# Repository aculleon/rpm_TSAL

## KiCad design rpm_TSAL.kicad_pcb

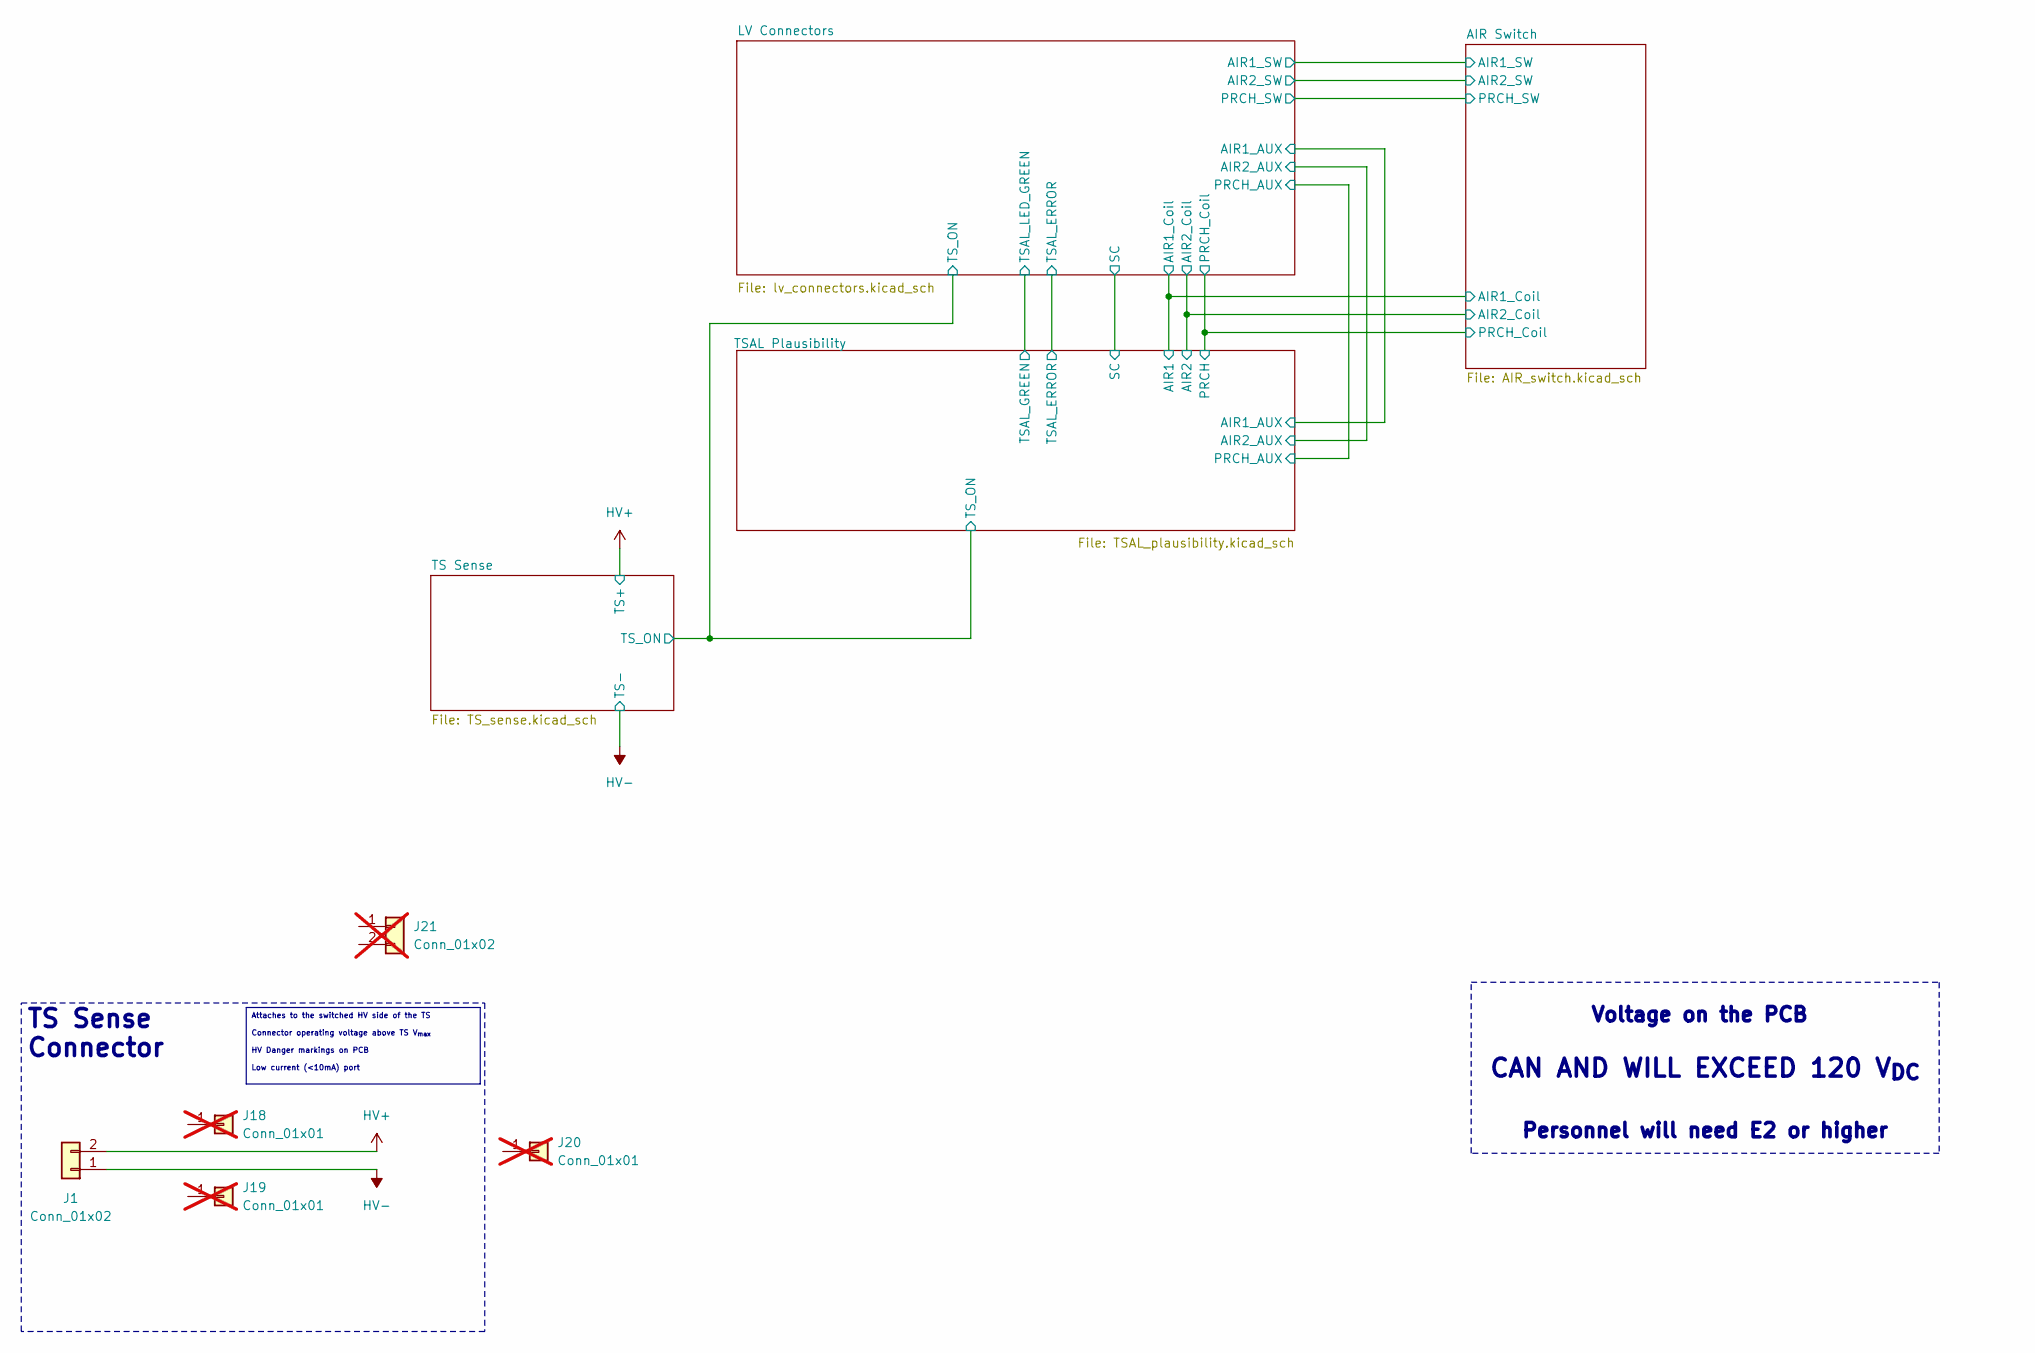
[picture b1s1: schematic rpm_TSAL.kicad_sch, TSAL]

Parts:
J1: Conn_01x02; 657002130101; Mouser 710-657002130101
J18, J19, J20: Conn_01x01; Mouser 710-65730513722DEC; not fitted
J21: Conn_01x02; Mouser 710-657002150201; not fitted

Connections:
HV+: J1.2; also elsewhere on the board
HV-: J1.1; also elsewhere on the board

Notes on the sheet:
_{Voltage on the PCB } CAN AND WILL EXCEED 120 V_{DC} _{Personnel will need E2 or higher}
Attaches to the switched HV side of the TS Connector operating voltage above TS V_{max} HV Danger markings on PCB Low current (<10mA) port
TS Sense Connector

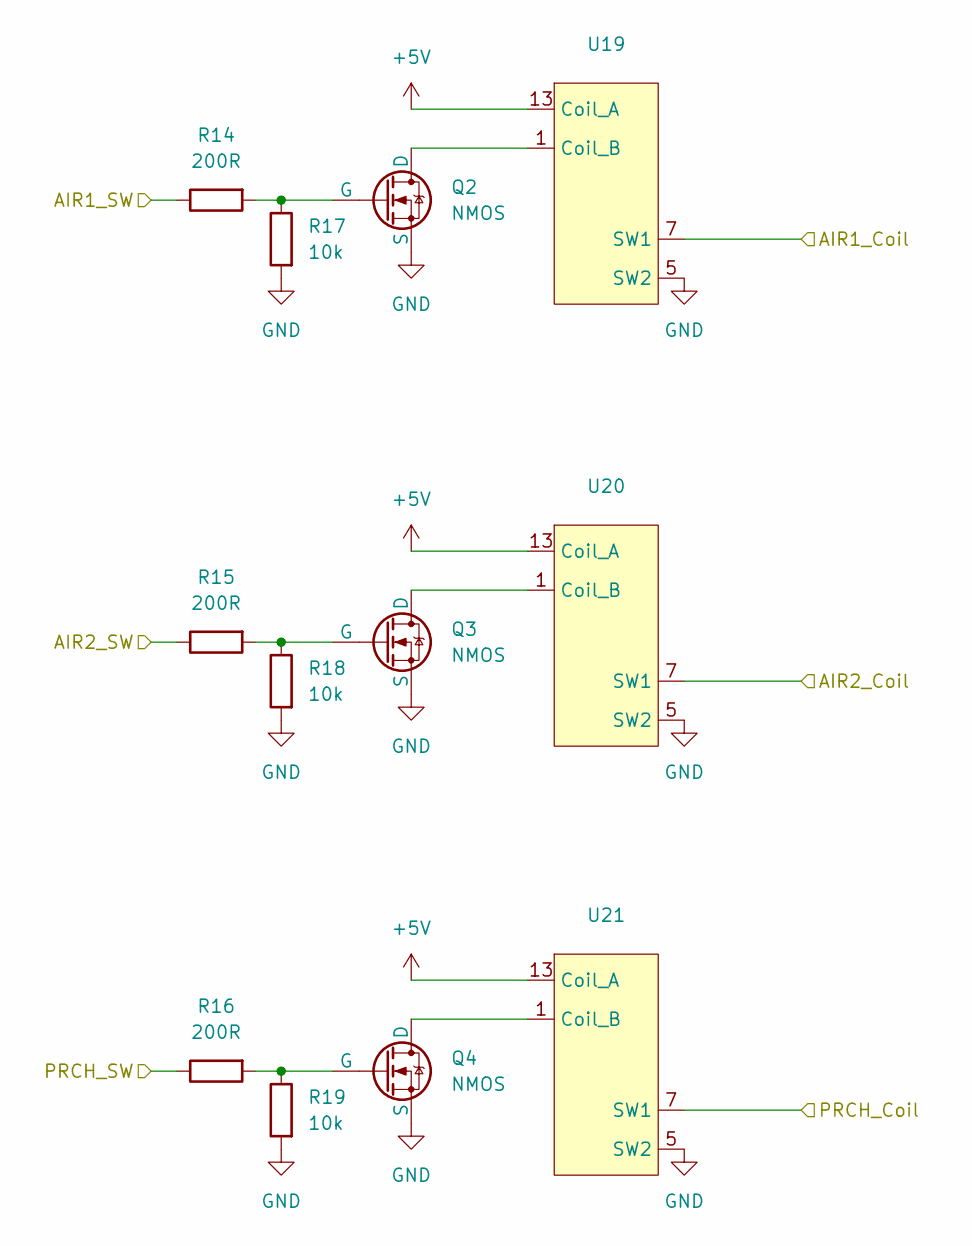
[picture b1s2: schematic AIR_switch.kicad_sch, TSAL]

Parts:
Q2, Q3, Q4: NMOS; SOT-23-3; Mouser 726-BSS316NH6327
R14, R15, R16: 200R; R_0603_1608Metric
R17, R18, R19: 10k; R_0603_1608Metric
U19, U20, U21: AZ9371

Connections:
+5V: U19.13 (Coil_A), U20.13 (Coil_A), U21.13 (Coil_A); also elsewhere on the board
/AIR Switch/AIR1_Coil: U19.7 (SW1); also elsewhere on the board
/AIR Switch/AIR1_SW: R14.1; also elsewhere on the board
/AIR Switch/AIR2_Coil: U20.7 (SW1); also elsewhere on the board
/AIR Switch/AIR2_SW: R15.1; also elsewhere on the board
/AIR Switch/PRCH_Coil: U21.7 (SW1); also elsewhere on the board
/AIR Switch/PRCH_SW: R16.1; also elsewhere on the board
GND: Q2.3 (S), Q3.3 (S), Q4.3 (S), R17.2, R18.2, R19.2, U19.5 (SW2), U20.5 (SW2), U21.5 (SW2); also elsewhere on the board
unnamed: Q2.1 (D), U19.1 (Coil_B)
unnamed: Q2.2 (G), R14.2, R17.1
unnamed: Q3.1 (D), U20.1 (Coil_B)
unnamed: Q3.2 (G), R15.2, R18.1
unnamed: Q4.1 (D), U21.1 (Coil_B)
unnamed: Q4.2 (G), R16.2, R19.1

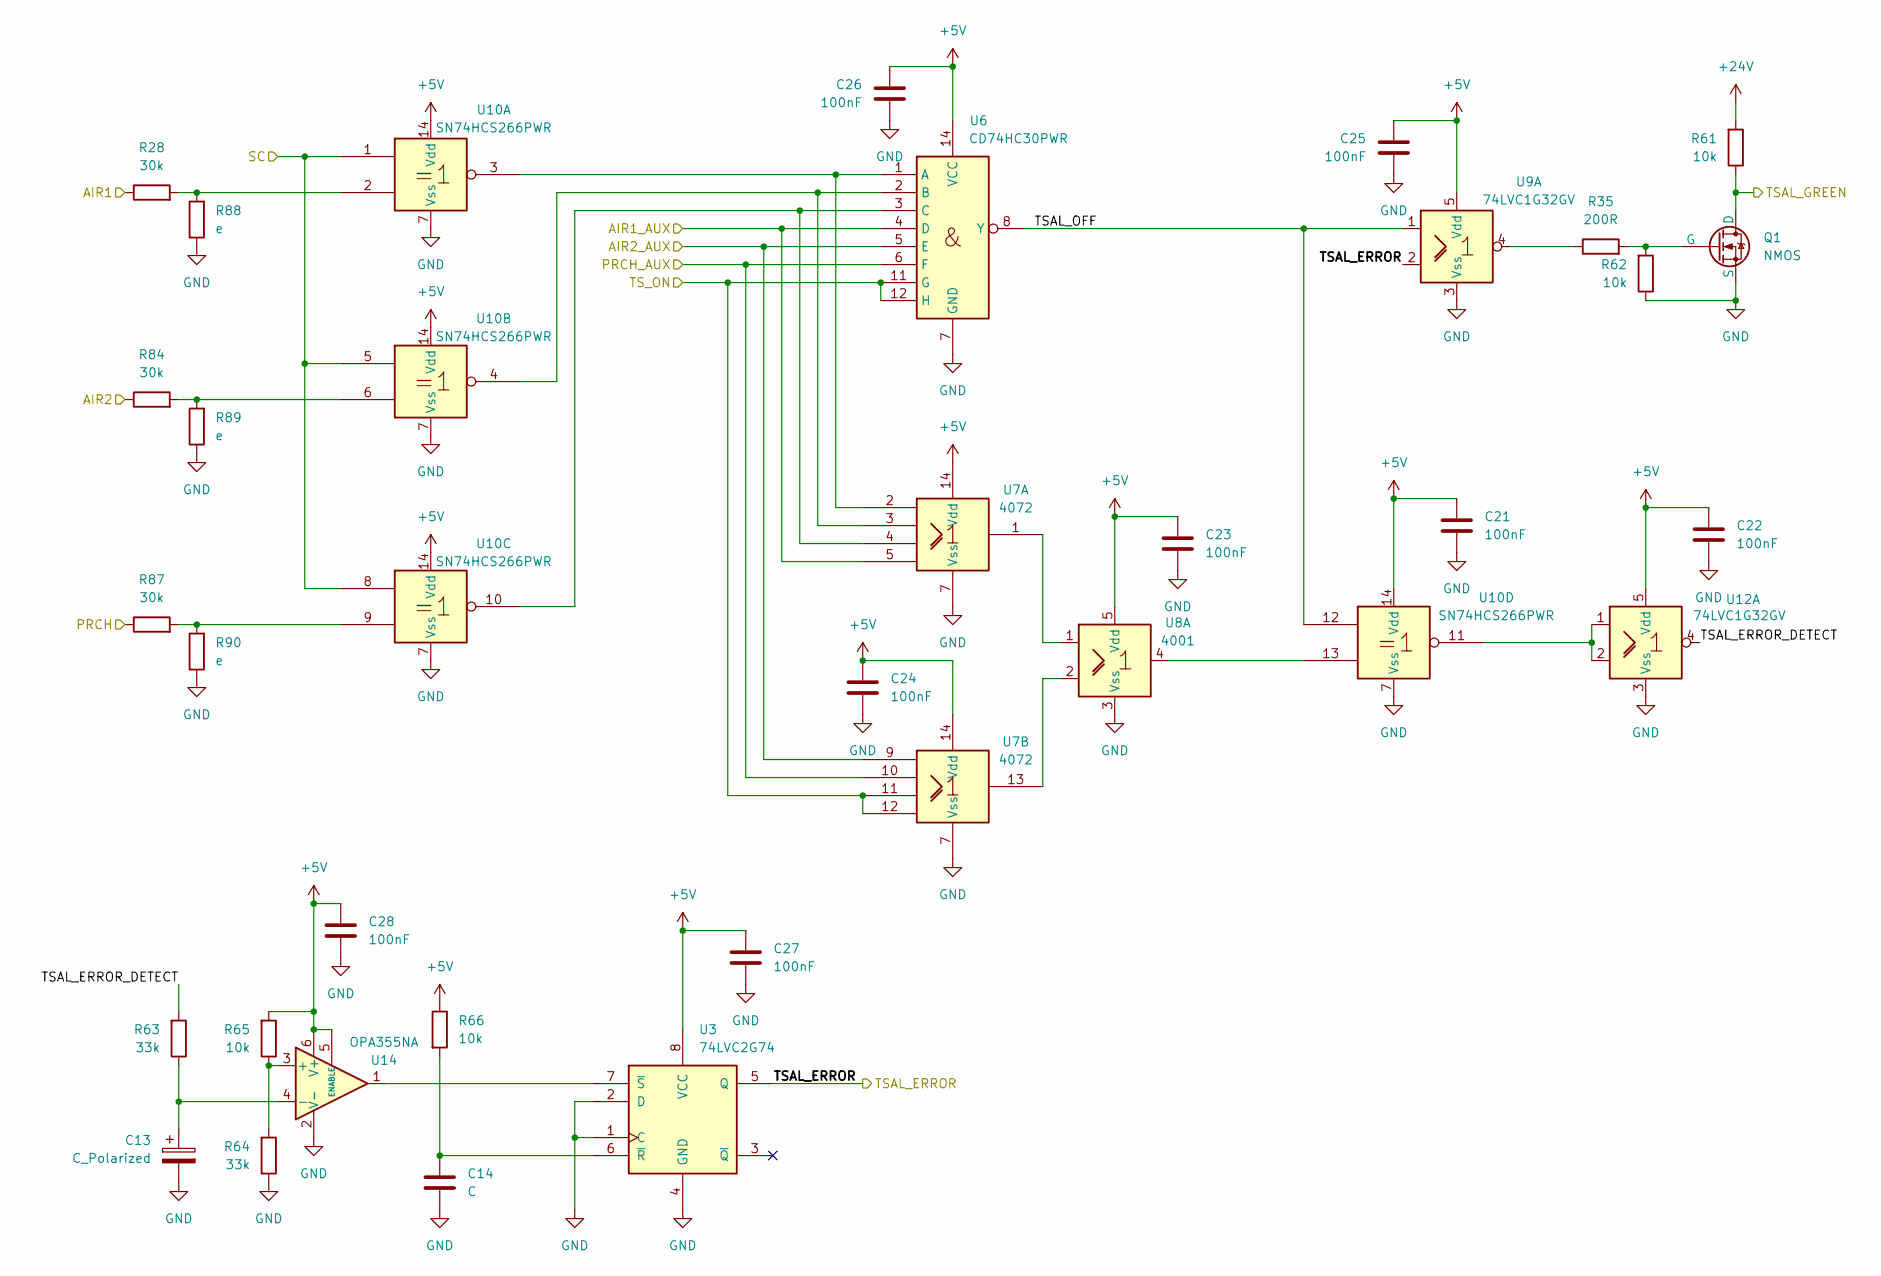
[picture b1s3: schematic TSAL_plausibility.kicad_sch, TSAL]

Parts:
C13: C_Polarized; C_0603_1608Metric
C14: C; C_0603_1608Metric
C21, C22, C23, C24, C25, C26, C27, C28: 100nF; C_0603_1608Metric
Q1: NMOS; SOT-23-3; Mouser 726-BSS316NH6327
R28, R84, R87: 30k; R_0603_1608Metric
R35: 200R; R_0603_1608Metric
R61, R62, R65, R66: 10k; R_0603_1608Metric
R63, R64: 33k; R_0603_1608Metric
R88, R89, R90: e; R_0603_1608Metric
U3: 74LVC2G74; TSSOP-8_3x3mm_P0.65mm; Mouser 771-74LVC2G74DP-G
U6: CD74HC30PWR; TSSOP-14_4.4x5mm_P0.65mm; Mouser 595-CD74HC30PWR
U7: 4072; TSSOP-14_4.4x5mm_P0.65mm; Mouser 595-CD4072BPW
U8: 4001; SC-74A-5_1.55x2.9mm_P0.95mm; Mouser 771-LVC1G32GV125
U9, U12: 74LVC1G32GV; SC-74A-5_1.55x2.9mm_P0.95mm; Mouser 771-LVC1G32GV125
U10: SN74HCS266PWR; TSSOP-14_4.4x5mm_P0.65mm; Mouser 595-SN74HCS266PWR
U14: OPA355NA; SOT-23-6; Mouser 595-OPA355NA/3K

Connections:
+5V: C21.1, C22.1, C23.1, C24.1, C25.1, C26.1, C27.1, C28.1, R65.2, R66.1, U3.8 (VCC), U6.14 (VCC), U7.14 (Vdd), U8.5 (Vdd), U9.5 (Vdd), U10.14 (Vdd), U12.5 (Vdd), U14.5 (ENABLE), U14.6 (V+); also elsewhere on the board
+24V: R61.2; also elsewhere on the board
/AIR Switch/AIR1_Coil: R28.1; also elsewhere on the board
/AIR Switch/AIR2_Coil: R84.1; also elsewhere on the board
/AIR Switch/PRCH_Coil: R87.1; also elsewhere on the board
/LV Connectors/AIR1_AUX: U6.4 (D), U7.5; also elsewhere on the board
/LV Connectors/AIR2_AUX: U6.5 (E), U7.9; also elsewhere on the board
/LV Connectors/PRCH_AUX: U6.6 (F), U7.10; also elsewhere on the board
/LV Connectors/SC: U10.1, U10.5, U10.8; also elsewhere on the board
/LV Connectors/TSAL_LED_GREEN: Q1.1 (D), R61.1; also elsewhere on the board
/LV Connectors/TS_ON: U6.11 (G), U6.12 (H), U7.11, U7.12; also elsewhere on the board
/TSAL Plausibility/TSAL_ERROR: U3.5 (Q), U9.2; also elsewhere on the board
/TSAL Plausibility/TSAL_ERROR_DETECT: R63.2, U12.4
/TSAL Plausibility/TSAL_OFF: U6.8 (Y), U9.1, U10.12
GND: C13.2, C14.2, C21.2, C22.2, C23.2, C24.2, C25.2, C26.2, C27.2, C28.2, Q1.3 (S), R62.1, R64.1, R88.1, R89.1, R90.1, U3.1 (C), U3.2 (D), U3.4 (GND), U6.7 (GND), U7.7 (Vss), U8.3 (Vss), U9.3 (Vss), U10.7 (Vss), U12.3 (Vss), U14.2 (V-); also elsewhere on the board
unnamed: Q1.2 (G), R35.2, R62.2
unnamed: R28.2, R88.2, U10.2
unnamed: R35.1, U9.4
unnamed: R84.2, R89.2, U10.6
unnamed: R87.2, R90.2, U10.9
unnamed: C14.1, R66.2, U3.6 (~R)
unnamed: U3.7 (~S), U14.1
unnamed: U6.1 (A), U7.2, U10.3
unnamed: U6.2 (B), U7.3, U10.4
unnamed: U6.3 (C), U7.4, U10.10
unnamed: U7.1, U8.1
unnamed: U7.13, U8.2
unnamed: U10.11, U12.1, U12.2
unnamed: U8.4, U10.13
unnamed: R64.2, R65.1, U14.3 (+)
unnamed: C13.1, R63.1, U14.4 (-)

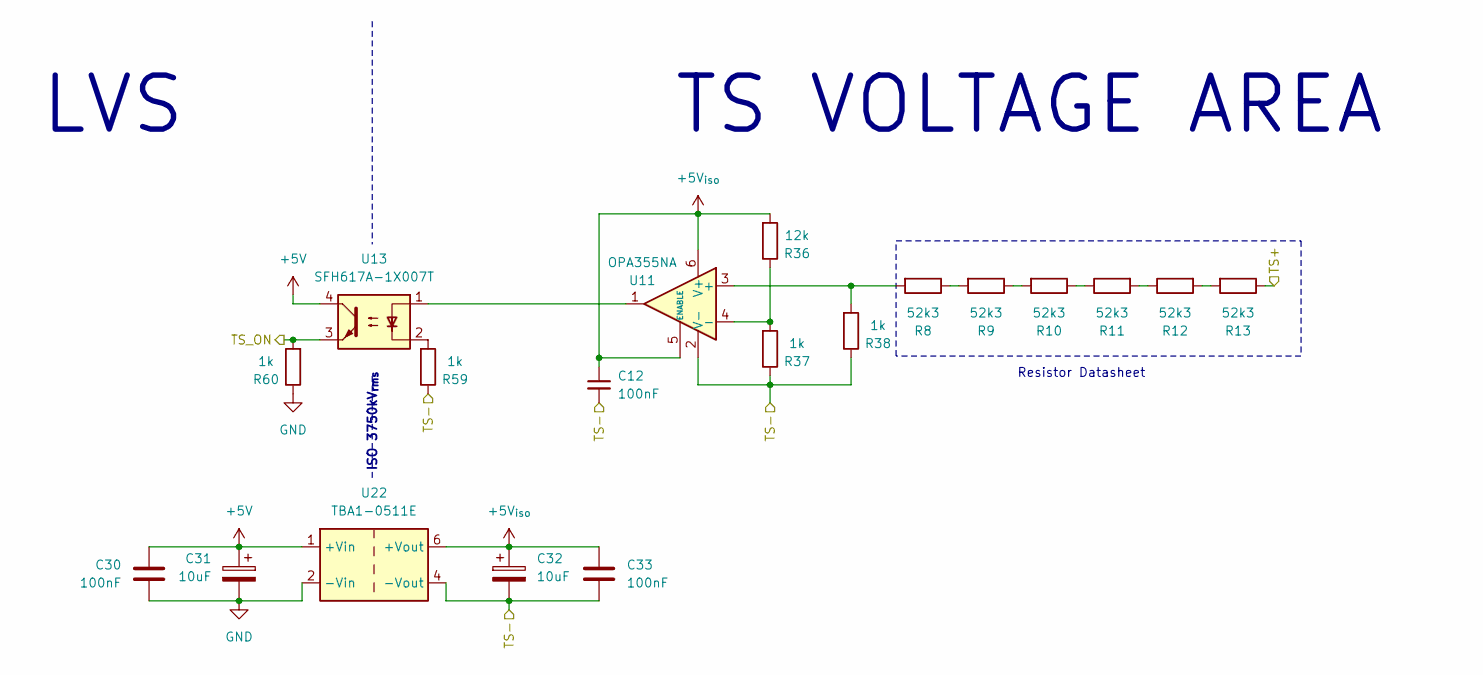
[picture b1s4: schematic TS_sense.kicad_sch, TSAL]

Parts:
C12, C30, C33: 100nF; C_0603_1608Metric
C31, C32: 10uF; C_0603_1608Metric
R8, R9, R10, R11, R12, R13: 52k3; R_0805_2012Metric; Mouser 603-RT0805DRD0752K3L
R36: 12k; R_0603_1608Metric
R37, R38, R59, R60: 1k; R_0603_1608Metric
U11: OPA355NA; SOT-23-6; Mouser 595-OPA355NA/3K
U13: SFH617A-1X007T; SMDIP-4_W9.53mm_Clearance8mm; Mouser 710-140357145300
U22: TBA1-0511E; Converter_DCDC_TRACO_TBA1-xxxxE_Single_THT; Mouser 495-TBA1-0511E

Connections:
+5V: C30.1, C31.1, U13.4, U22.1 (+Vin); also elsewhere on the board
+5V_{iso}: C12.1, C32.1, C33.1, R36.2, U11.5 (ENABLE), U11.6 (V+), U22.6 (+Vout)
/LV Connectors/TS_ON: R60.2, U13.3; also elsewhere on the board
GND: C30.2, C31.2, R60.1, U22.2 (-Vin); also elsewhere on the board
HV+: R13.1; also elsewhere on the board
HV-: C12.2, C32.2, C33.2, R37.1, R38.1, R59.1, U11.2 (V-), U22.4 (-Vout); also elsewhere on the board
unnamed: R8.1, R9.2
unnamed: R10.1, R11.1
unnamed: R9.1, R10.2
unnamed: R11.2, R12.1
unnamed: R12.2, R13.2
unnamed: R59.2, U13.2
unnamed: R8.2, R38.2, U11.3 (+)
unnamed: R36.1, R37.2, U11.4 (-)
unnamed: U11.1, U13.1

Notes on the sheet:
TS VOLTAGE AREA
ISO 3750kV_{rms}
LVS
Resistor Datasheet

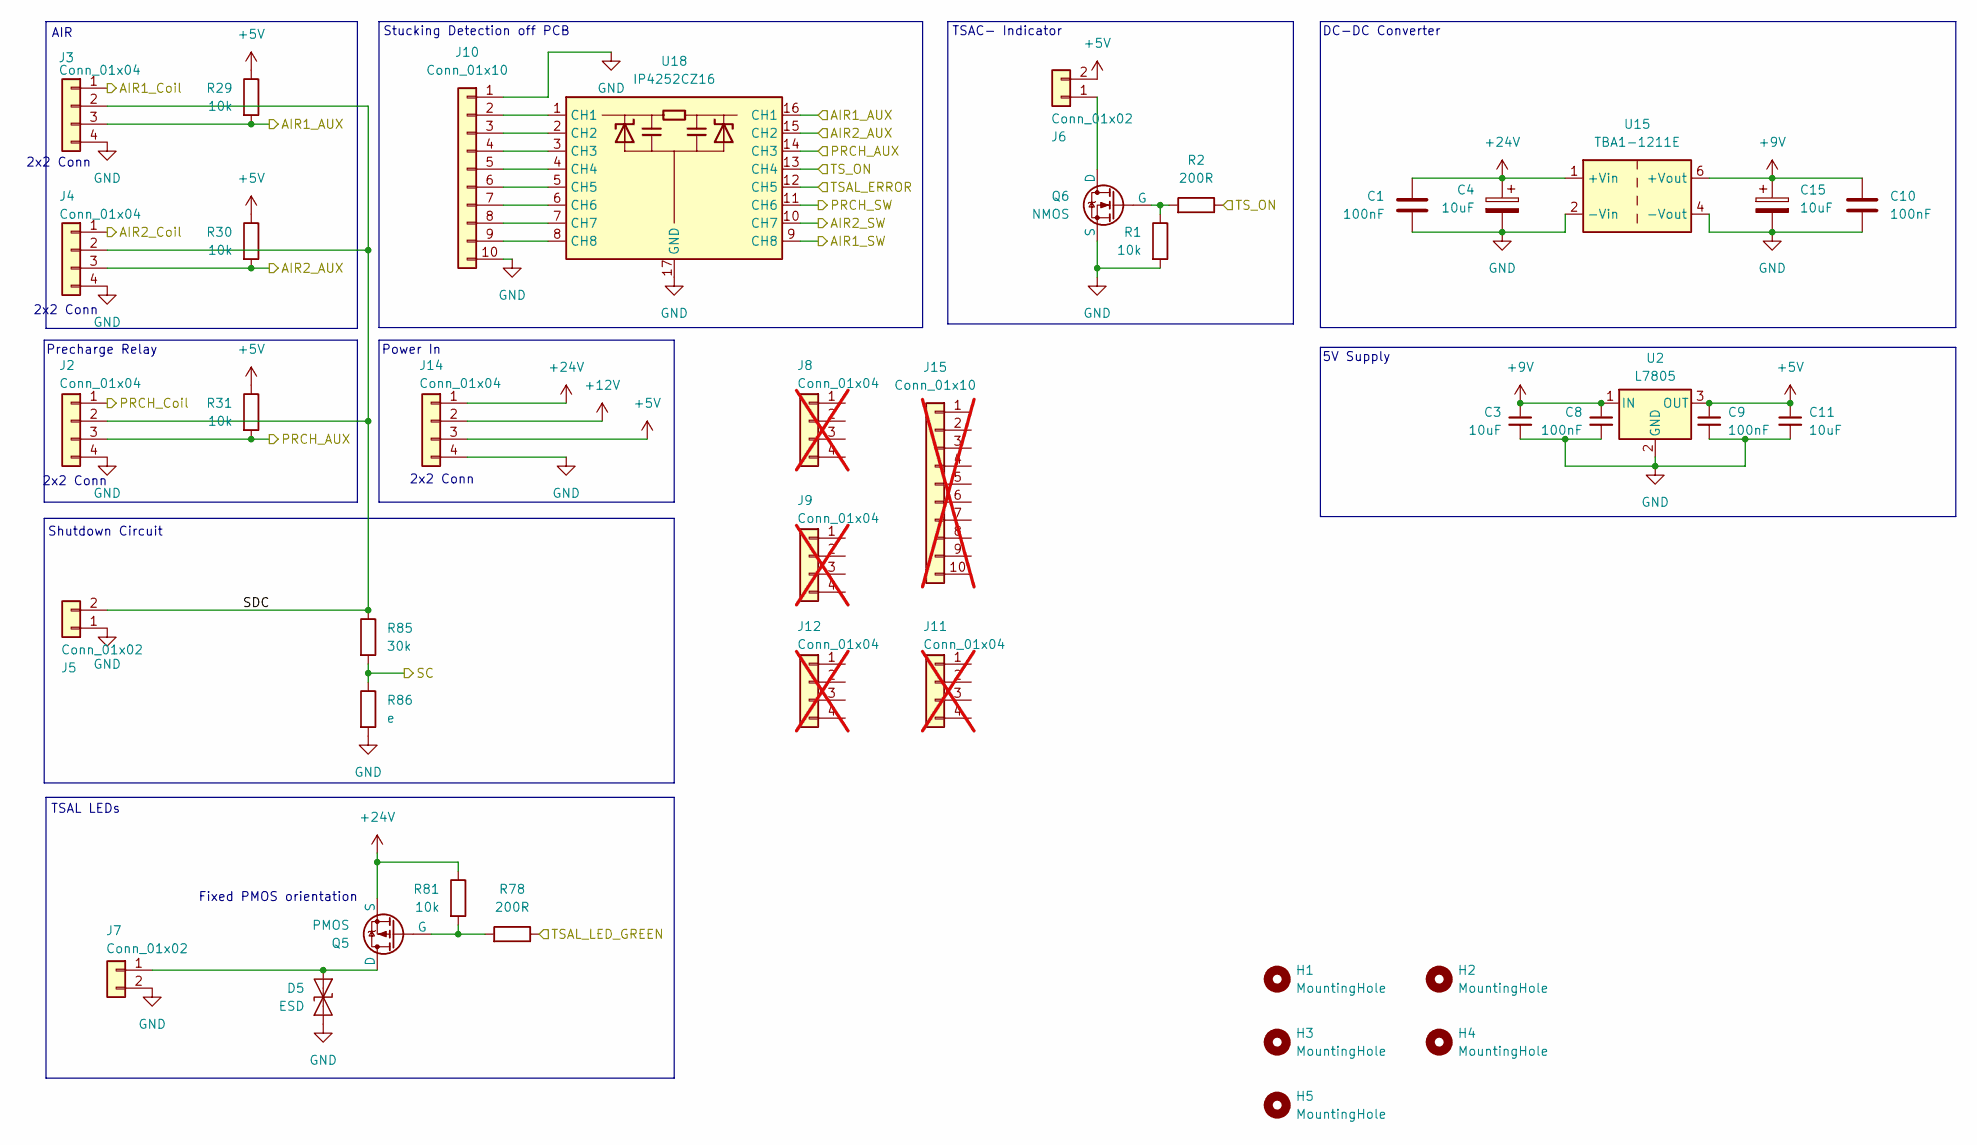
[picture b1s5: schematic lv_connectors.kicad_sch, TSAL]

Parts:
C1, C8, C9, C10: 100nF; C_0603_1608Metric
C3, C4, C11, C15: 10uF; C_0603_1608Metric
D5: ESD; Infineon_SG-WLL-2-3_0.58x0.28_P0.36mm; Mouser 726-ESD131B1W0201E63
H1, H2, H3, H4, H5: MountingHole; MountingHole_3.2mm_M3
J2, J3, J4, J14: Conn_01x04; 66200421022; Mouser 710-66200421022
J5, J7: Conn_01x02; 66200211024
J6: Conn_01x02; JST_XH_B2B-XH-A_1x02_P2.50mm_Vertical
J8, J9, J11, J12: Conn_01x04; Mouser 710-662004113322; not fitted
J10: Conn_01x10; IDC-Header_2x05_P2.54mm_Latch6.5mm_Vertical; Mouser 710-61201022021
J15: Conn_01x10; Mouser 710-61201023021; not fitted
Q5: PMOS; SOT-23-3
Q6: NMOS; SOT-23-3; Mouser 726-BSS316NH6327
R1, R29, R30, R31, R81: 10k; R_0603_1608Metric
R2, R78: 200R; R_0603_1608Metric
R85: 30k; R_0603_1608Metric
R86: e; R_0603_1608Metric
U2: L7805; TO-252-2; Mouser 511-L7805ABD2T-TR
U15: TBA1-1211E; Converter_DCDC_TRACO_TBA1-xxxxE_Single_THT; Mouser 495-TBA1-1219HI
U18: IP4252CZ16; Nexperia_HUSON-16_USON-16-1EP_1.35x3.3mm_P0.4mm_EP0.4x2.8mm; Mouser 771-IP4252CZ168TTL1

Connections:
+5V: C9.1, C11.1, J6.2, J14.3, R29.1, R30.1, R31.1, U2.3 (OUT); also elsewhere on the board
+9V: C3.1, C8.1, C10.1, C15.1, U2.1 (IN), U15.6 (+Vout)
+12V: J14.2
+24V: C1.1, C4.1, J14.1, Q5.3 (S), R81.1, U15.1 (+Vin); also elsewhere on the board
/AIR Switch/AIR1_Coil: J3.1; also elsewhere on the board
/AIR Switch/AIR1_SW: U18.9 (CH8); also elsewhere on the board
/AIR Switch/AIR2_Coil: J4.1; also elsewhere on the board
/AIR Switch/AIR2_SW: U18.10 (CH7); also elsewhere on the board
/AIR Switch/PRCH_Coil: J2.1; also elsewhere on the board
/AIR Switch/PRCH_SW: U18.11 (CH6); also elsewhere on the board
/LV Connectors/AIR1_AUX: J3.3, R29.2, U18.16 (CH1); also elsewhere on the board
/LV Connectors/AIR2_AUX: J4.3, R30.2, U18.15 (CH2); also elsewhere on the board
/LV Connectors/PRCH_AUX: J2.3, R31.2, U18.14 (CH3); also elsewhere on the board
/LV Connectors/SC: R85.2, R86.1; also elsewhere on the board
/LV Connectors/SDC: J2.2, J3.2, J4.2, J5.2, R85.1
/LV Connectors/TSAL_LED_GREEN: R78.1; also elsewhere on the board
/LV Connectors/TS_ON: R2.1, U18.13 (CH4); also elsewhere on the board
/TSAL Plausibility/TSAL_ERROR: U18.12 (CH5); also elsewhere on the board
GND: C1.2, C3.2, C4.2, C8.2, C9.2, C10.2, C11.2, C15.2, D5.1 (A1), J2.4, J3.4, J4.4, J5.1, J7.2, J10.1, J10.10, J14.4, Q6.3 (S), R1.2, R86.2, U2.2 (GND), U15.2 (-Vin), U15.4 (-Vout), U18.17 (GND); also elsewhere on the board
unnamed: D5.2 (A2), J7.1, Q5.1 (D)
unnamed: J6.1, Q6.1 (D)
unnamed: J10.2, U18.1 (CH1)
unnamed: J10.3, U18.2 (CH2)
unnamed: J10.4, U18.3 (CH3)
unnamed: J10.5, U18.4 (CH4)
unnamed: J10.6, U18.5 (CH5)
unnamed: J10.7, U18.6 (CH6)
unnamed: J10.8, U18.7 (CH7)
unnamed: J10.9, U18.8 (CH8)
unnamed: Q5.2 (G), R78.2, R81.2
unnamed: Q6.2 (G), R1.1, R2.2

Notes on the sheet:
2x2 Conn
DC-DC Converter
Power In
Stucking Detection off PCB
TSAC- Indicator
TSAL LEDs
5V Supply
Shutdown Circuit
AIR
Precharge Relay
Fixed PMOS orientation

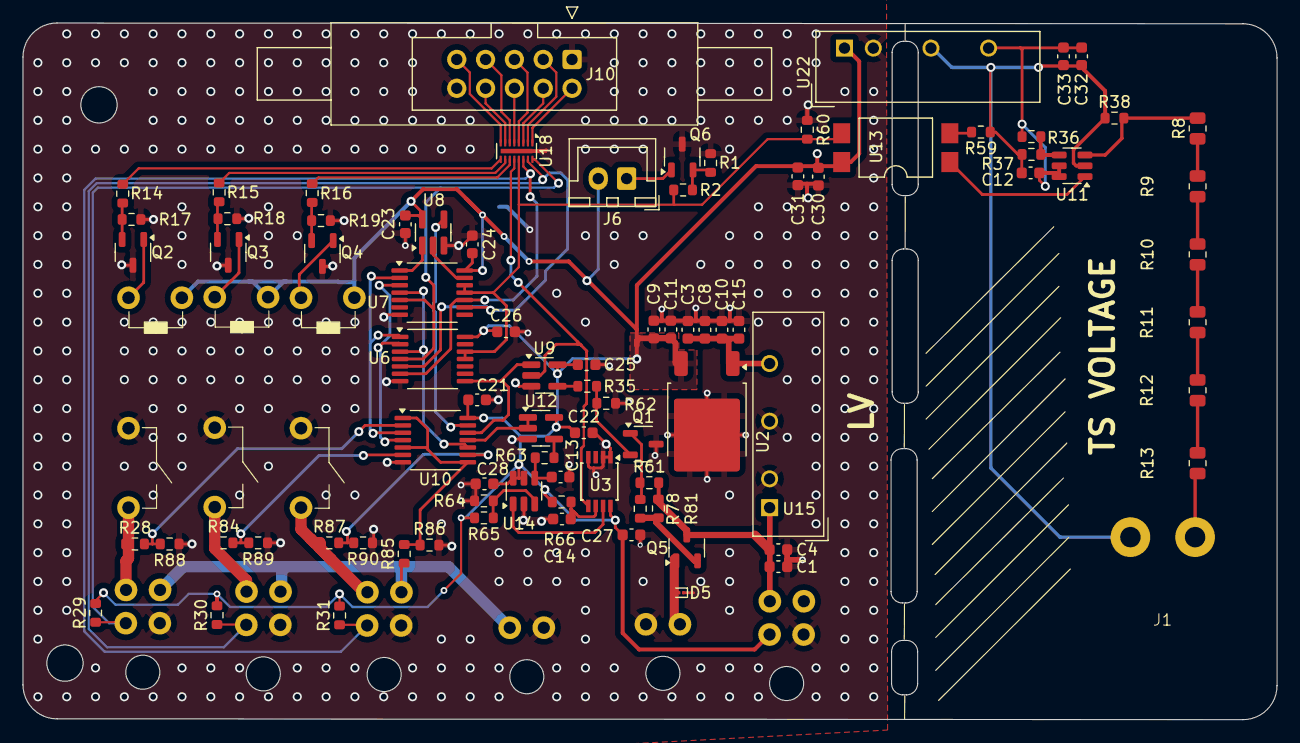
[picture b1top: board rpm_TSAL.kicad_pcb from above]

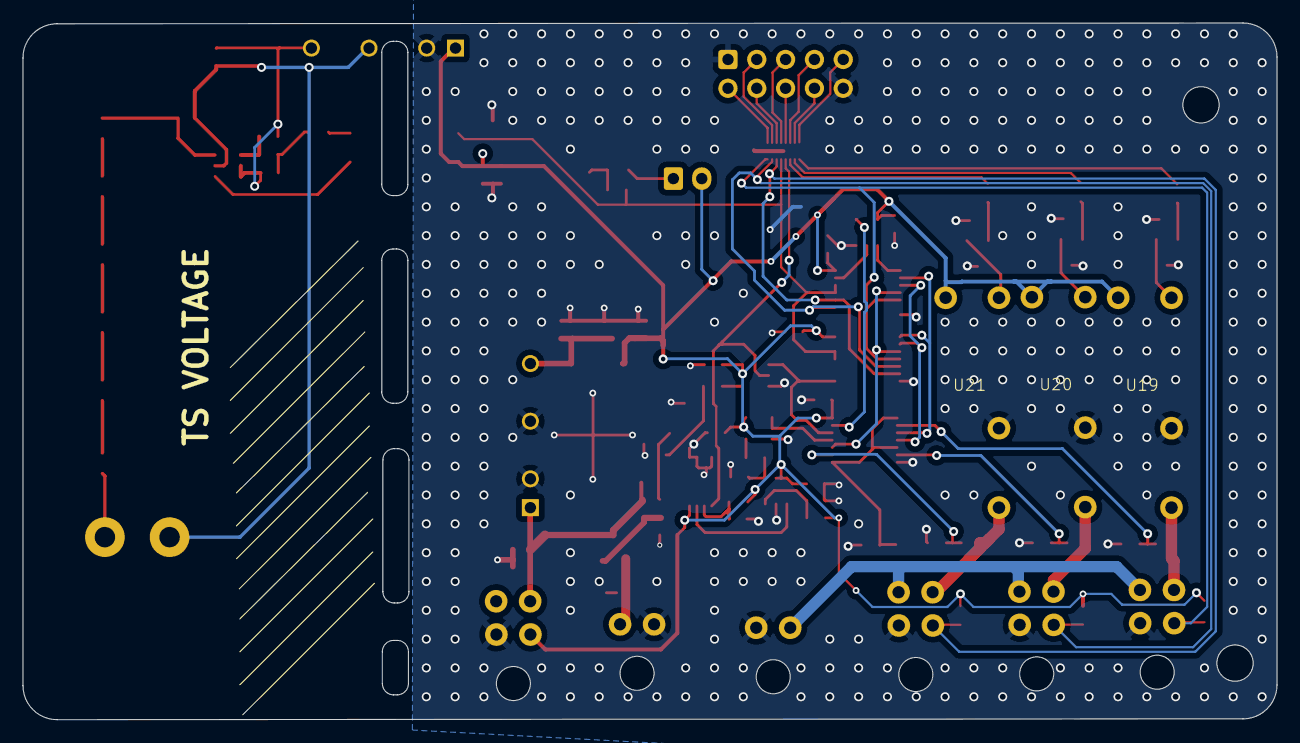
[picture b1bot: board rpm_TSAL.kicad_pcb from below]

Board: 2 copper layers, 110.5 x 61.4 mm, 100 parts (3 on the bottom side), 66 nets.

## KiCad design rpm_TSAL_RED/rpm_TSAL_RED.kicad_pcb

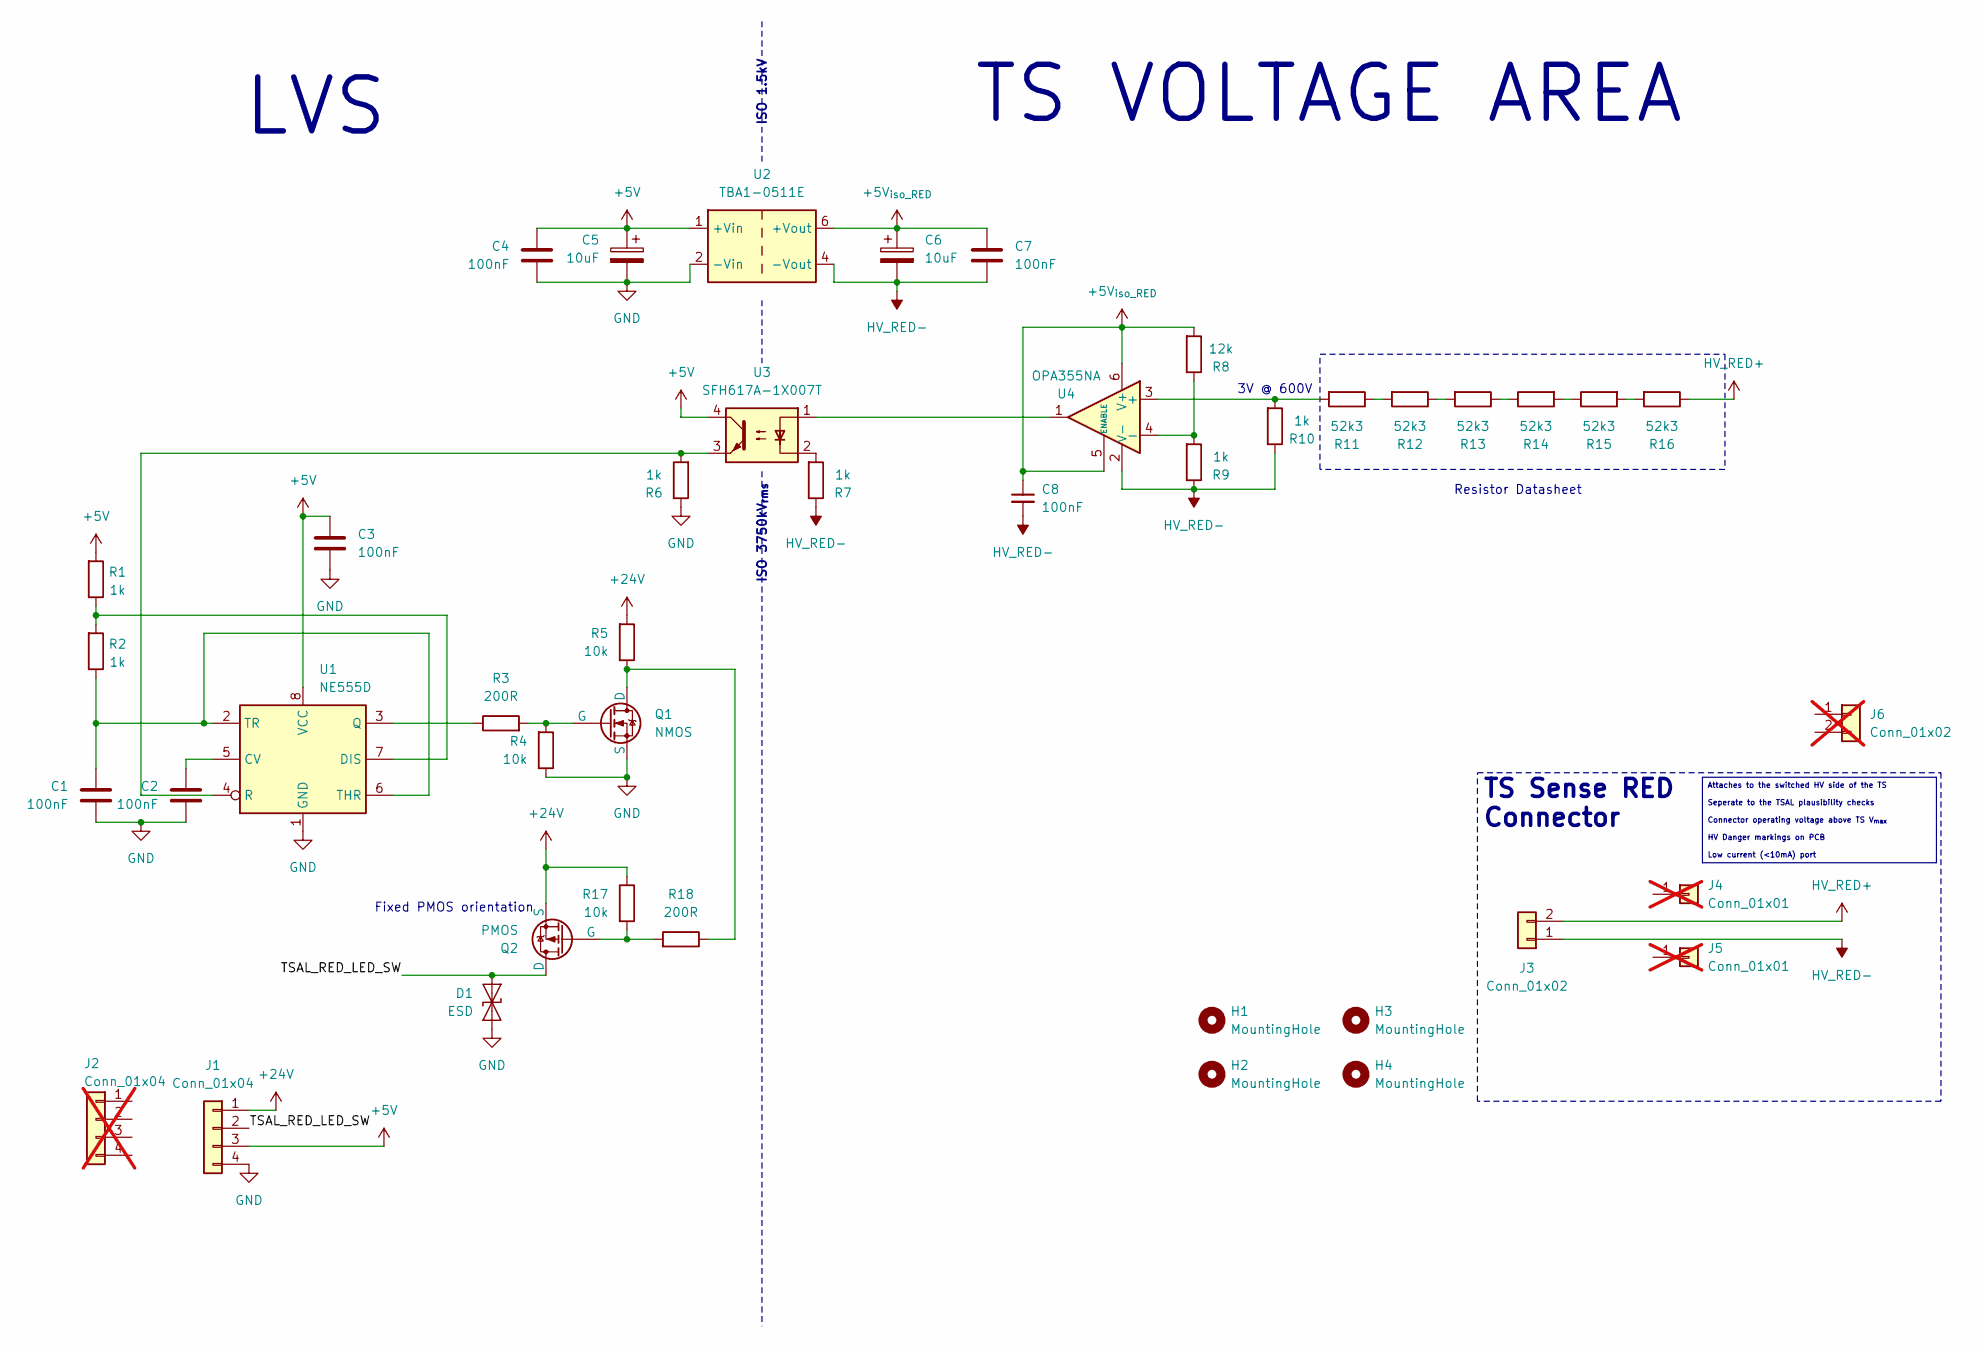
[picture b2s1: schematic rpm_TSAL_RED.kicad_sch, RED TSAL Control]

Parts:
C1, C2, C3, C4, C7, C8: 100nF; C_0603_1608Metric
C5, C6: 10uF; C_0603_1608Metric
D1: ESD; Infineon_SG-WLL-2-3_0.58x0.28_P0.36mm; Mouser 726-ESD131B1W0201E63
H1, H2, H3, H4: MountingHole; MountingHole_3.2mm_M3_DIN965
J1: Conn_01x04; 66200411022; Mouser 710-66200421022
J2: Conn_01x04; Mouser 710-662004113322; not fitted
J3: Conn_01x02; 657002130101; Mouser 710-657002130101
J4, J5: Conn_01x01; Mouser 710-65730513722DEC; not fitted
J6: Conn_01x02; Mouser 710-657002150201; not fitted
Q1: NMOS; SOT-23-3; Mouser 726-BSS316NH6327
Q2: PMOS; SOT-23-3
R1, R2, R6, R7, R9, R10: 1k; R_0603_1608Metric
R3, R18: 200R; R_0603_1608Metric
R4, R5, R17: 10k; R_0603_1608Metric
R8: 12k; R_0603_1608Metric
R11, R12, R13, R14, R15, R16: 52k3; R_0805_2012Metric; Mouser 603-RT0805DRD0752K3L
U1: NE555D; SOIC-8_3.9x4.9mm_P1.27mm; Mouser 595-NE555DR
U2: TBA1-0511E; Converter_DCDC_TRACO_TBA1-xxxxE_Single_THT; Mouser 495-TBA1-0511E
U3: SFH617A-1X007T; SMDIP-4_W9.53mm_Clearance8mm; Mouser 710-140357145300
U4: OPA355NA; SOT-23-6; Mouser 595-OPA355NA/3K

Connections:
+5V: C3.1, C4.1, C5.1, J1.3, R1.2, U1.8 (VCC), U2.1 (+Vin), U3.4
+5V_{iso_RED}: C6.1, C7.1, C8.1, R8.2, U2.6 (+Vout), U4.5 (ENABLE), U4.6 (V+)
+24V: J1.1, Q2.3 (S), R5.2, R17.1
/TSAL_RED_LED_SW: D1.2 (A2), J1.2, Q2.1 (D)
GND: C1.2, C2.2, C3.2, C4.2, C5.2, D1.1 (A1), J1.4, Q1.3 (S), R4.1, R6.1, U1.1 (GND), U2.2 (-Vin)
HV_RED+: J3.2, R16.1
HV_RED-: C6.2, C7.2, C8.2, J3.1, R7.1, R9.1, R10.1, U2.4 (-Vout), U4.2 (V-)
unnamed: Q1.1 (D), R5.1, R18.1
unnamed: Q1.2 (G), R3.2, R4.2
unnamed: Q2.2 (G), R17.2, R18.2
unnamed: R7.2, U3.2
unnamed: R11.1, R12.2
unnamed: R12.1, R13.2
unnamed: R13.1, R14.1
unnamed: R14.2, R15.1
unnamed: R15.2, R16.2
unnamed: C2.1, U1.5 (CV)
unnamed: R1.1, R2.2, U1.7 (DIS)
unnamed: R3.1, U1.3 (Q)
unnamed: R6.2, U1.4 (R), U3.3
unnamed: C1.1, R2.1, U1.2 (TR), U1.6 (THR)
unnamed: U3.1, U4.1
unnamed: R10.2, R11.2, U4.3 (+)
unnamed: R8.1, R9.2, U4.4 (-)

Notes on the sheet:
Attaches to the switched HV side of the TS Seperate to the TSAL plausibility checks Connector operating voltage above TS V_{max} HV Danger markings on PCB Low current (<10mA) port
Fixed PMOS orientation
TS VOLTAGE AREA
ISO 3750kV_{rms}
3V @ 600V
TS Sense RED Connector
Resistor Datasheet
ISO 1.5kV
LVS

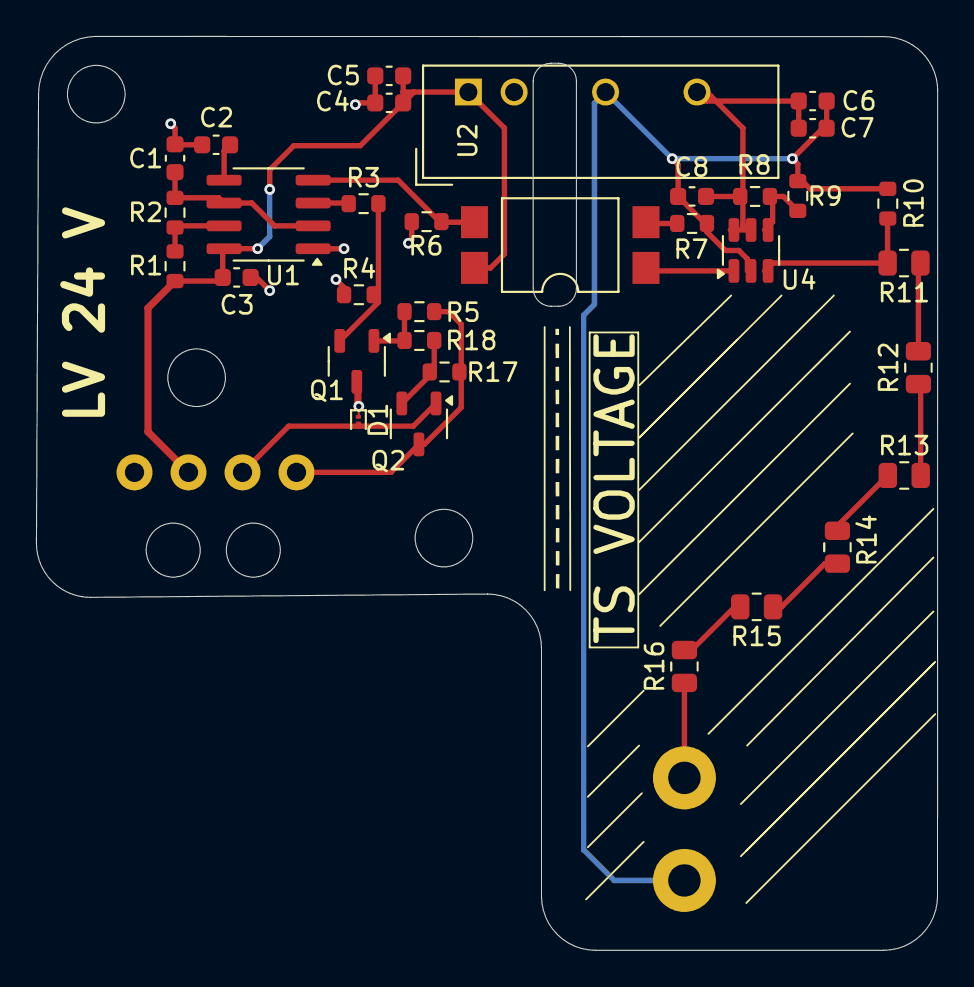
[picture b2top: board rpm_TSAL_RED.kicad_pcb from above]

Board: 2 copper layers, 50.1 x 50.8 mm, 39 parts (0 on the bottom side), 24 nets.

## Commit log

2024-07-11 init
2024-07-11 Saved. Initial Structure done.
2024-07-11 added OPA and HV Resistors
2024-07-11 Added *.lck to gitignore
2024-07-14 Changes to Pinout pending
2024-07-14 added files
2024-07-15 Changed Layout
2024-07-15 Checked Rules. Looks good. Need to fix AIR Aux detection. Need to Fix Coil Activation. Need to add SCS Failure Output and SCS Failure Inhibiter
2024-07-15 Added new Subsheet
2024-07-15 Added decoupling Caps
2024-07-15 Updated pdf
2024-07-15 Added Rules
2024-07-15 Submission Ready. ESF 15.07.24
2024-07-15 Added Subschematic
2024-07-16 TS Detection routing
2024-07-17 Misc.
2024-07-22 TSAL Rev 0.2
2024-07-23 Added Seperate Project
2024-07-24 Added Sub project
2024-07-24 Connector Updated
2024-07-24 Routing of AIR Relay
2024-07-24 misc
2024-07-26 Added TSAC Indicator with PSU
2024-07-26 Added ESF comments
2024-08-01 ordered
